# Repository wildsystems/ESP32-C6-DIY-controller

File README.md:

# ESP32-C6 Sensor Controller

## 📊 Description
This project is a basic controller built around the ESP32-C6-MINI-1, designed for monitoring and managing temperature, humidity, flow, and PWM-based sensors/actuators. It supports direct connection for four NTC thermistors, one DHT21 sensor, a 1-Wire bus with DS18B20, one pulse input for a Hall effect flow sensor, one PWM input, one PWM output, and two relay outputs. Additionally, it includes a USB-C connector for power and communication, supporting USB-CDC (virtual serial) and JTAG debugging.

---

## 🔧 Key Features

| Component               | Description                                            |
|------------------------|--------------------------------------------------------|
| 🌡️ 4x NTC Inputs         | Analog reading via voltage divider with fixed resistor |
| 🔋 1x DHT21 (AM2301)     | Temperature and humidity sensor                        |
| ❄️ 1x DS18B20 (1-Wire)   | Bus for Dallas 1-Wire temperature sensors              |
| 🚿 1x Flow Sensor (HALL) | Pulse-based flow measurement                           |
| 🎛️ 1x PWM Input           | Frequency or duty-cycle based input                   |
| 🔉 1x PWM Output          | PWM signal output for motor/valve control             |
| ⚙️ 2x Relay Outputs       | Load control (e.g. pump, valve)                        |
| 🔌 1x USB-C Connector     | Power input, USB-CDC serial, and JTAG debug support   |

---

## ⚙️ Pin Assignment (ESP32-C6-MINI-1 Safe GPIOs)

| Function                | GPIO Pin | Notes                                      |
|------------------------|----------|---------------------------------------------|
| NTC1 (analog in)       | GPIO1    | ADC1 channel                                |
| NTC2                   | GPIO3    | ADC1 channel                                |
| NTC3                   | GPIO4    | ADC1 channel                                |
| NTC4                   | GPIO5    | ADC1 channel                                |
| DHT21 / DS18B20        | GPIO6    | 4.7k pull-up to 3.3V                        |
| Flow Sensor (input)    | GPIO7    | Interrupt on rising edge                    |
| PWM Input              | GPIO14   | Timer capture capable                       |
| PWM Output             | GPIO15   | LEDC or MCPWM output                        |
| Relay 1 (output)       | GPIO18   | Load control                                |
| Relay 2                | GPIO19   | Load control                                |
| USB D+                 | GPIO13   | Native USB data+ (shared with UART RX)      |
| USB D−                 | GPIO12   | Native USB data−                            |
---

## 📝 Notes

- All GPIOs used are considered safe for ESP32-C6-MINI-1 boot operation.
- NTC sensors are read via the internal ADC1.
- DHT21 requires at least a 2-second interval between readings.
- DS18B20 supports multiple sensors on a single 1-Wire bus.
- PWM input can be measured using capture/timer functionality.
- PWM output can be generated via LEDC or MCPWM peripheral.
- Relay outputs can be connected to opto-isolated relay modules.
- USB-C port supports 5V input and USB communication (CDC, JTAG).

---

## 🚀 Applications

- Fermentation controller
- Room temperature and humidity monitoring
- Smart irrigation systems
- General home automation
- Fan or valve modulation via PWM
- USB-connected data acquisition

---

## License

This hardware project is licensed under the **CERN-OHL-P v2** (Permissive).
- You may use, modify, and distribute the design files.
- You are free to create derivative works and even release them under a closed license.
- No warranty is provided.

Full text of the license can be found in the [LICENSE](./LICENSE) file.

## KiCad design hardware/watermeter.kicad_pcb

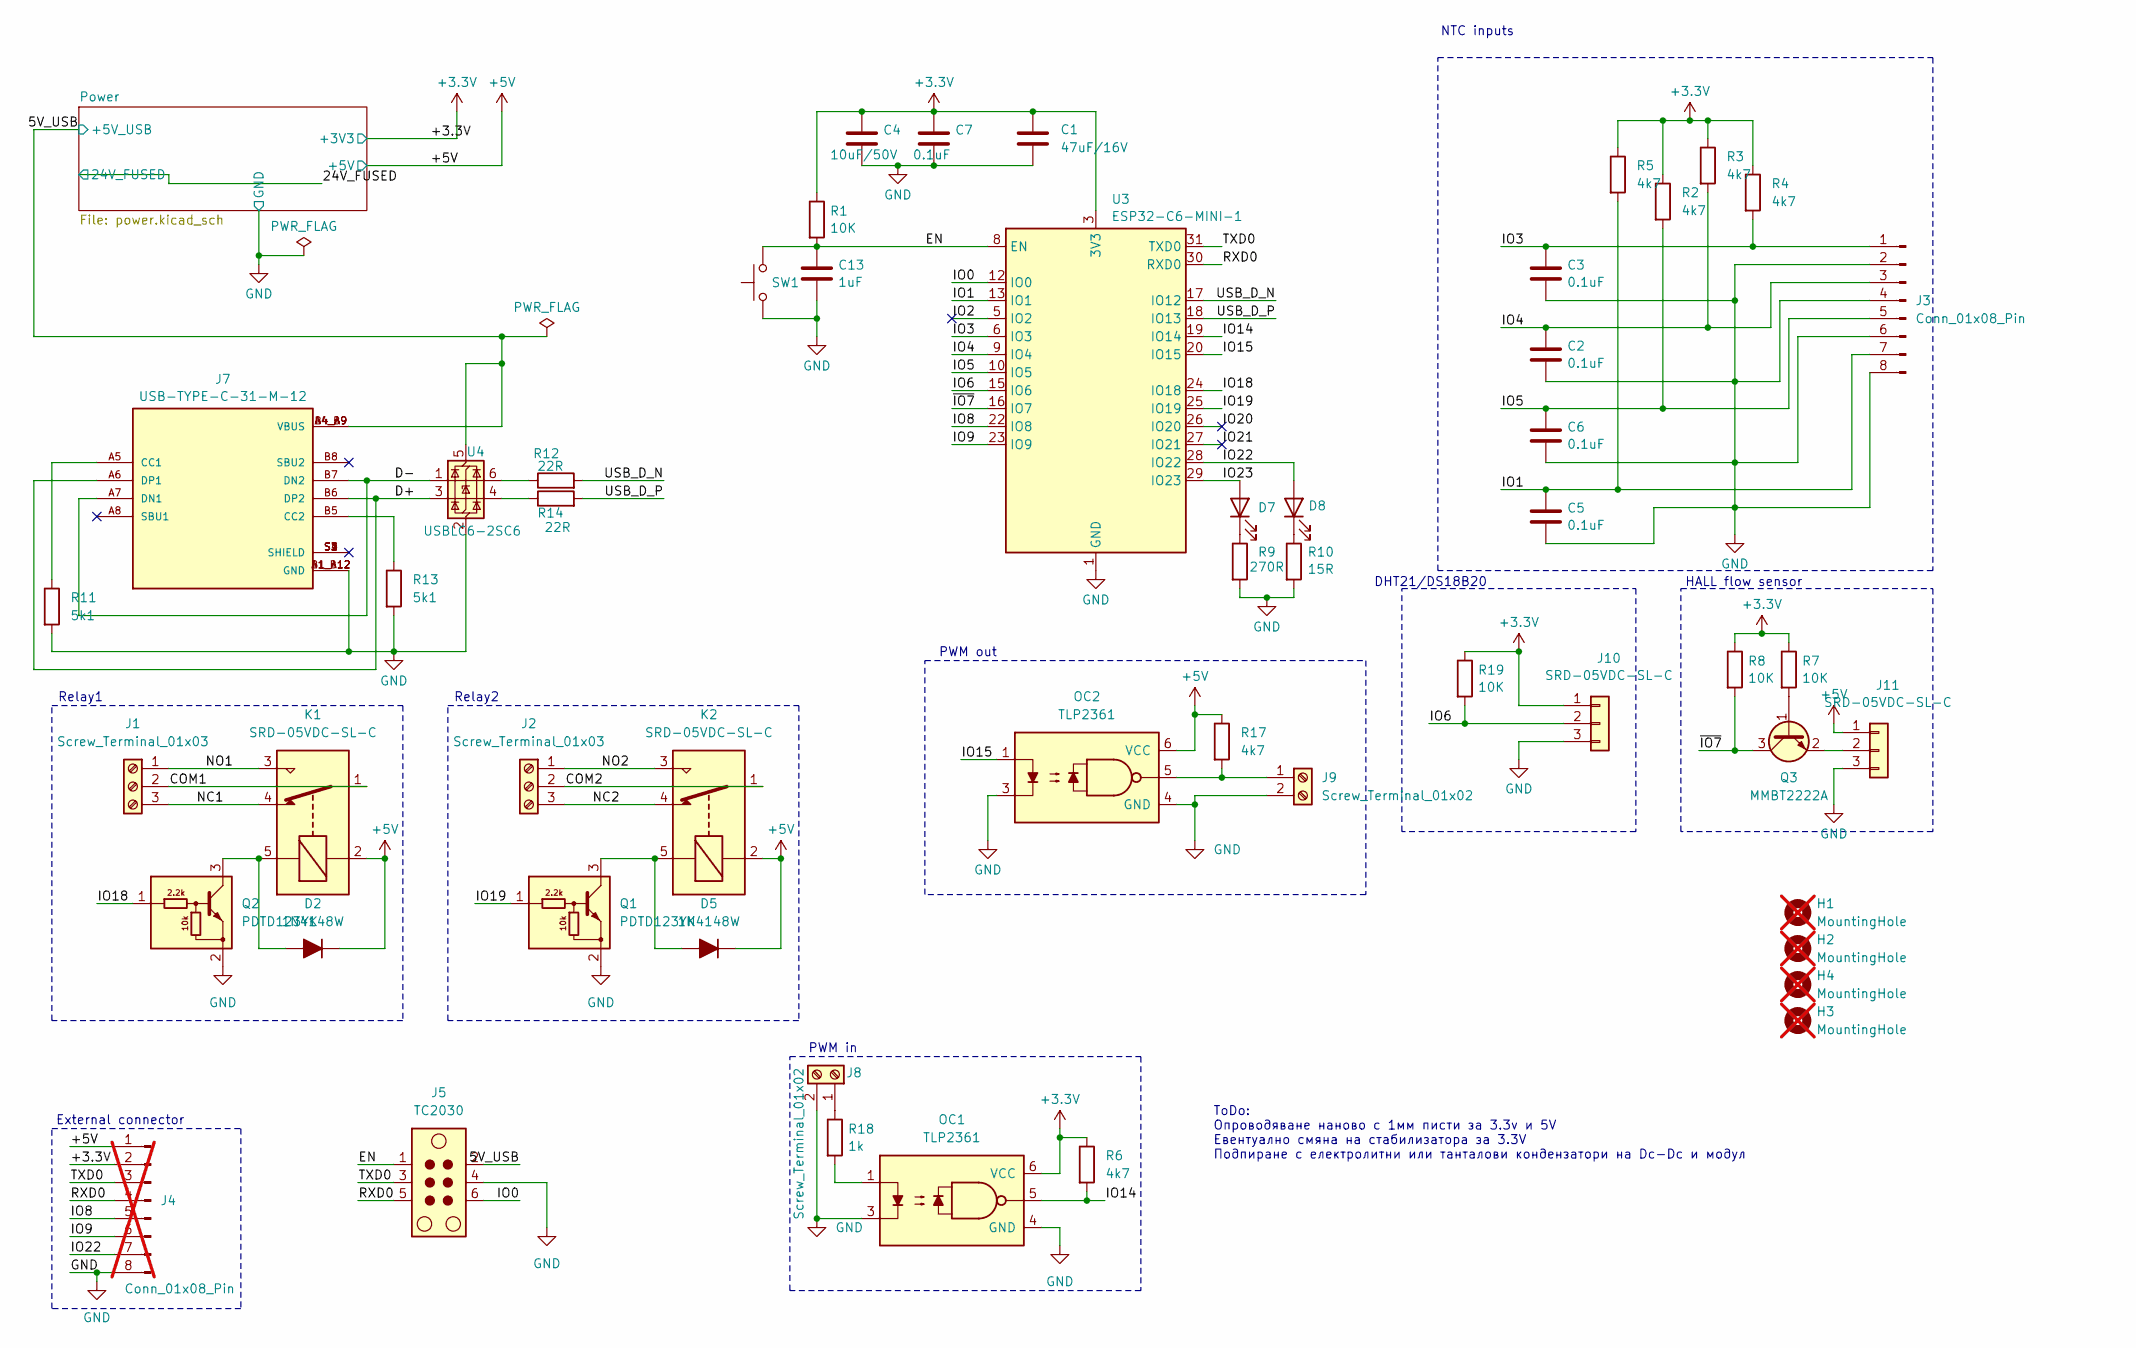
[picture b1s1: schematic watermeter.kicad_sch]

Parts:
C1: 47uF/16V; C_1206_3216Metric; LCSC Part # C96123
C2, C3, C5, C6, C7: 0.1uF; C_1206_3216Metric; LCSC Part # C24497
C4: 10uF/50V; C_1206_3216Metric; LCSC Part # C13585
C13: 1uF; C_0402_1005Metric; LCSC Part # C14445
D2, D5: 1N4148W; D_SOD-323_HandSoldering; LCSC Part # C2128
D7: KT-0805G; LED_0805_2012Metric; LCSC Part # C2297
D8: KT-0805B; D_0805_2012Metric; LCSC Part # C2293
H1, H2, H3, H4: MountingHole; MountingHole_3.2mm_M3_ISO7380; not fitted
J1, J2: Screw_Terminal_01x03; TerminalBlock_Phoenix_MKDS-1,5-3-5.08_1x03_P5.08mm_Horizont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; LCSC Part # C2915640
J3: Conn_01x08_Pin; TerminalBlock_Phoenix_MKDS-1,5-8-5.08_1x08_P5.08mm_Horizont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; LCSC Part # C5143711
J4: Conn_01x08_Pin; PinHeader_1x08_P2.54mm_Vertical; not fitted
J5: TC2030; Tag-Connect_TC2030-IDC-NL_2x03_P1.27mm_Vertical
J7: USB-TYPE-C-31-M-12; USB-HRO_TYPE-C-31-M-12; LCSC Part # C165948
J8, J9: Screw_Terminal_01x02; TerminalBlock_Phoenix_MKDS-1,5-2-5.08_1x02_P5.08mm_Horizont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; LCSC Part # C2915639
J10, J11: SRD-05VDC-SL-C; TerminalBlock_Phoenix_MKDS-1,5-3-5.08_1x03_P5.08mm_Horizont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; LCSC Part # C2915640
K1, K2: SRD-05VDC-SL-C; Relay_SPDT_SANYOU_SRD_Series_Form_C; LCSC Part # C35449
OC1, OC2: TLP2361; SO-5_4.4x3.6mm_P1.27mm; LCSC Part # C107626
Q1, Q2: PDTD123YK; SC-59; LCSC Part # C295450
Q3: MMBT2222A; SOT-23
R1, R7, R8, R19: 10K; R_0805_2012Metric; LCSC Part # C17414
R2, R3, R4, R5, R6, R17: 4k7; R_0805_2012Metric; LCSC Part # C17673
R9: 270R; LED_0603; LCSC Part # C22966
R10: 15R; R_0805_2012Metric; LCSC Part # C17480
R11, R13: 5k1; R_0805_2012Metric; LCSC Part # C27834
R12, R14: 22R; R_0805_2012Metric; LCSC Part # C17561
R18: 1k; R_0805_2012Metric; LCSC Part # C17513
SW1: Reboot; SW-SMD_4P-L5.1-W5.1-P3.70-LS6.5-TL-2; LCSC Part # C318884
U3: ESP32-C6-MINI-1; LCSC Part # C5736265
U4: USBLC6-2SC6; SOT-23-6; LCSC Part # C7519

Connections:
+3.3V: C1.1, C4.1, C7.1, J4.2, J10.1, OC1.6 (VCC), R1.1, R2.1, R3.1, R4.1, R5.1, R6.1, R7.1, R8.1, R19.1, U3.3 (3V3); also elsewhere on the board
+5V: D2.1 (K), D5.1 (K), J4.1, J11.1, K1.2, K2.2, OC2.6 (VCC), R17.1; also elsewhere on the board
/5V_USB: J5.2, J7.A4_B9 (VBUS), J7.B4_A9 (VBUS), U4.5 (VBUS); also elsewhere on the board
/COM1: J1.2, K1.1
/COM2: J2.2, K2.1
/D+: J7.A6 (DP1), J7.B6 (DP2), U4.3 (I/O2)
/D-: J7.A7 (DN1), J7.B7 (DN2), U4.1 (I/O1)
/EN: C13.1, J5.1, R1.2, SW1.2, U3.8 (EN)
/IO0: J5.6, U3.12 (IO0)
/IO1: C5.1, J3.7, R5.2, U3.13 (IO1)
/IO2: U3.5 (IO2)
/IO3: C3.1, J3.1, R4.2, U3.6 (IO3)
/IO4: C2.1, J3.3, R3.2, U3.9 (IO4)
/IO5: C6.1, J3.5, R2.2, U3.10 (IO5)
/IO6: J10.2, R19.2, U3.15 (IO6)
/IO8: J4.5, U3.22 (IO8)
/IO9: J4.6, U3.23 (IO9)
/IO14: OC1.5, R6.2, U3.19 (IO14)
/IO15: OC2.1, U3.20 (IO15)
/IO18: Q2.1 (B), U3.24 (IO18)
/IO19: Q1.1 (B), U3.25 (IO19)
/IO20: U3.26 (IO20)
/IO21: U3.27 (IO21)
/IO22: D8.2 (A), J4.7, U3.28 (IO22)
/IO23: D7.2 (A), U3.29 (IO23)
/NC1: J1.3, K1.4
/NC2: J2.3, K2.4
/NO1: J1.1, K1.3
/NO2: J2.1, K2.3
/RXD0: J4.4, J5.5, U3.30 (RXD0)
/TXD0: J4.3, J5.3, U3.31 (TXD0)
/USB_D_N: R12.2, U3.17 (IO12)
/USB_D_P: R14.2, U3.18 (IO13)
/~IO7: Q3.3 (C), R8.2, U3.16 (IO7)
GND: C1.2, C2.2, C3.2, C4.2, C5.2, C6.2, C7.2, C13.2, J3.2, J3.4, J3.6, J3.8, J4.8, J5.4, J7.A1_B12 (GND), J7.B1_A12 (GND), J8.2, J9.2, J10.3, J11.3, OC1.3, OC1.4 (GND), OC2.3, OC2.4 (GND), Q1.2 (E), Q2.2 (E), R9.2, R10.2, R11.2, R13.2, SW1.1, U3.1 (GND), U3.2 (GND), U3.11 (GND), U3.14 (GND), U3.36 (GND), U3.37 (GND), U3.38 (GND), U3.39 (GND), U3.40 (GND), U3.41 (GND), U3.42 (GND), U3.43 (GND), U3.44 (GND), U3.45 (GND), U3.46 (GND), U3.47 (GND), U3.48 (GND), U3.49 (GND), U3.50 (GND), U3.51 (GND), U3.52 (GND), U3.53 (GND), U4.2 (GND); also elsewhere on the board
unnamed: D2.2 (A), K1.5, Q2.3 (C)
unnamed: D5.2 (A), K2.5, Q1.3 (C)
unnamed: D7.1 (K), R9.1
unnamed: D8.1 (K), R10.1
unnamed: J7.A5 (CC1), R11.1
unnamed: J7.B5 (CC2), R13.1
unnamed: J8.1, R18.1
unnamed: J9.1, OC2.5, R17.2
unnamed: J11.2, Q3.2 (E)
unnamed: OC1.1, R18.2
unnamed: Q3.1 (B), R7.2
unnamed: R12.1, U4.6 (I/O1)
unnamed: R14.1, U4.4 (I/O2)

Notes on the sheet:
NTC inputs
Relay1
PWM out
HALL flow sensor
External connector
Relay2
PWM in
ToDo: Опроводяване наново с 1мм писти за 3.3v и 5V Евентуално смяна на стабилизатора за 3.3V Подпиране с електролитни или танталови кондензатори на Dc-Dc и модул
DHT21/DS18B20

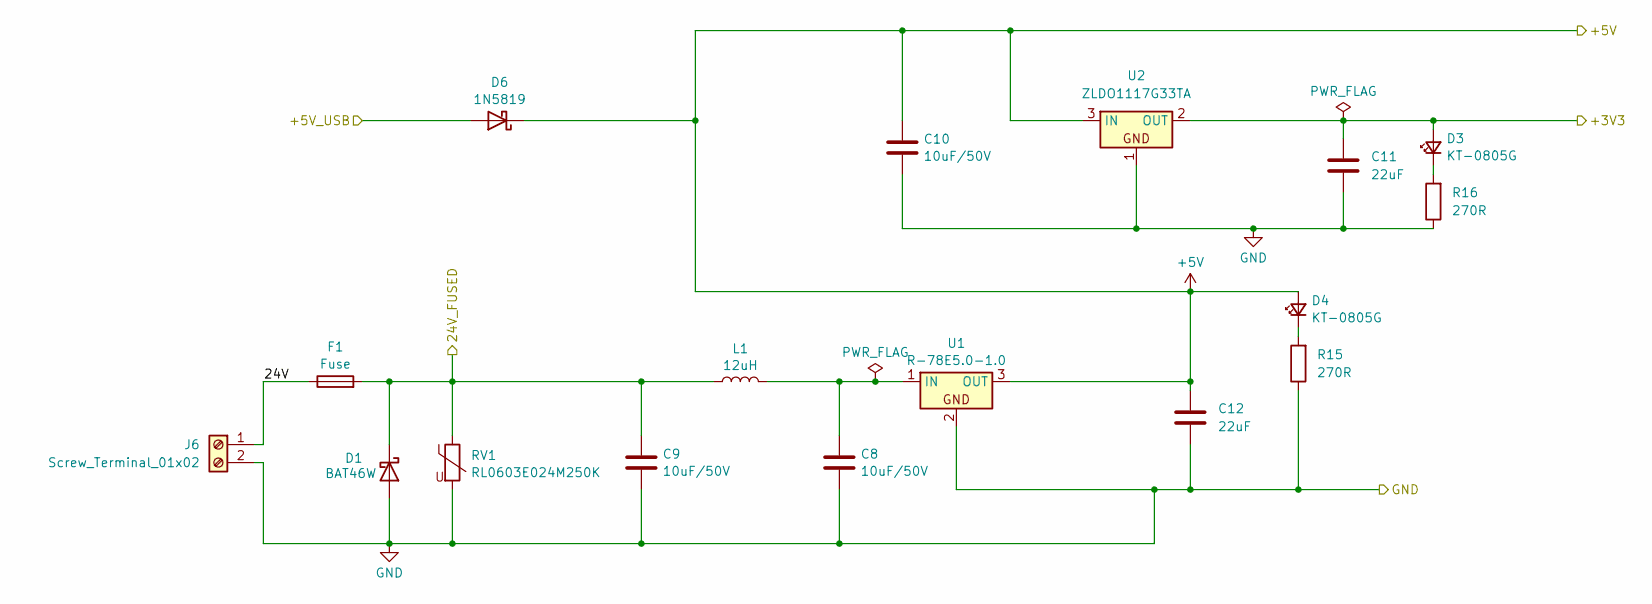
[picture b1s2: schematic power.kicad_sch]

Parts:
C8, C9, C10: 10uF/50V; C_1206_3216Metric; LCSC Part # C13585
C11, C12: 22uF; C_1206_3216Metric; LCSC Part # C12891
D1: BAT46W; D_SOD-123; LCSC Part # C7420332
D3, D4: KT-0805G; LED_0805_2012Metric; LCSC Part # C2297
D6: 1N5819; D_SOD-323_HandSoldering; LCSC Part # C191023
F1: Fuse; FUSE-TH_L24.4-W9.4-P22.60; LCSC Part # C717030
J6: Screw_Terminal_01x02; TerminalBlock_Phoenix_MKDS-1,5-2-5.08_1x02_P5.08mm_Horizont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; LCSC Part # C2915639
L1: 12uH; IND_ASPI-6045S-120M-T; LCSC Part # C168077
R15, R16: 270R; LED_0603; LCSC Part # C22966
RV1: RL0603E024M250K; D_0603_1608Metric; LCSC Part # C20966
U1: R-78E5.0-1.0; PWRM-TH_K78XX-500R3; LCSC Part # C22371890
U2: ZLDO1117G33TA; SOT-223-3_TabPin2; LCSC Part # C92102

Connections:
+3.3V: C11.1, D3.2 (A), U2.2 (OUT); also elsewhere on the board
+5V: C10.1, C12.1, D4.2 (A), D6.1 (K), U1.3 (OUT), U2.3 (IN); also elsewhere on the board
/5V_USB: D6.2 (A); also elsewhere on the board
/24V_FUSED: C9.1, D1.1 (K), F1.2, L1.1, RV1.1
/Power/24V: F1.1, J6.1
GND: C8.2, C9.2, C10.2, C11.2, C12.2, D1.2 (A), J6.2, R15.1, R16.1, RV1.2, U1.2, U2.1; also elsewhere on the board
unnamed: D3.1 (K), R16.2
unnamed: D4.1 (K), R15.2
unnamed: C8.1, L1.2, U1.1 (IN)

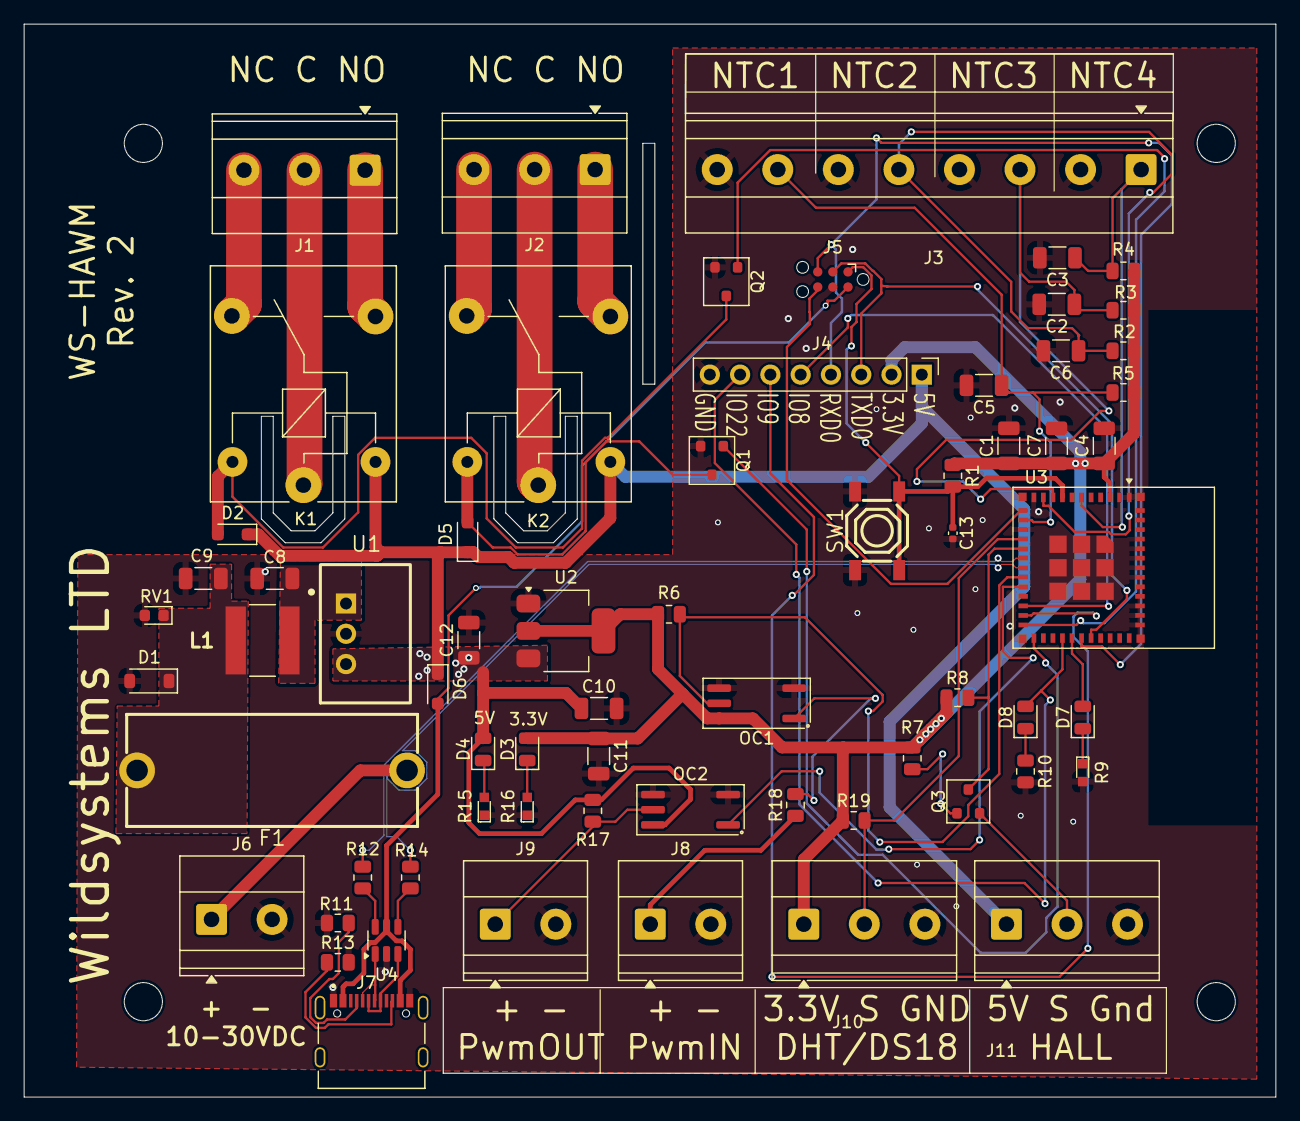
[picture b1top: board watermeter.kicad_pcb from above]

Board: 2 copper layers, 105.0 x 90.0 mm, 70 parts (0 on the bottom side), 50 nets.

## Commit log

2025-05-20 Initial import after reorganization
2025-06-01 Refactoring
2025-06-01 Schematics done
2025-06-02 Release hardware design v1.0 for manufacturing
2025-06-02 Cleanup
2025-06-14 fix: unstable power supply
2025-06-19 Board V2. fix: power supply fix: NTC noise suppression fix: Q1 and Q2 wrong pin numbers fix: Increased power trice width
2025-06-19 V2 gerber files
2025-06-27 small fixes
2025-07-04 Production - V2 Added: TagConnect port for fast firmware upload Fixes: Resistive diider fo hall sensor was replaced with transistor logic Refactoring for whole power supply Minimal track width 0.2mm 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
2025-08-16 Synced with V2 production README.md
2025-08-16 License added
2025-08-22 fix: gitignore for backup folders
